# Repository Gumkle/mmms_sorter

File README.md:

### Notes

STM32 Bluepill appears to have bad 3.3V regulator. It is recommended to use external power supply for 3.3V.

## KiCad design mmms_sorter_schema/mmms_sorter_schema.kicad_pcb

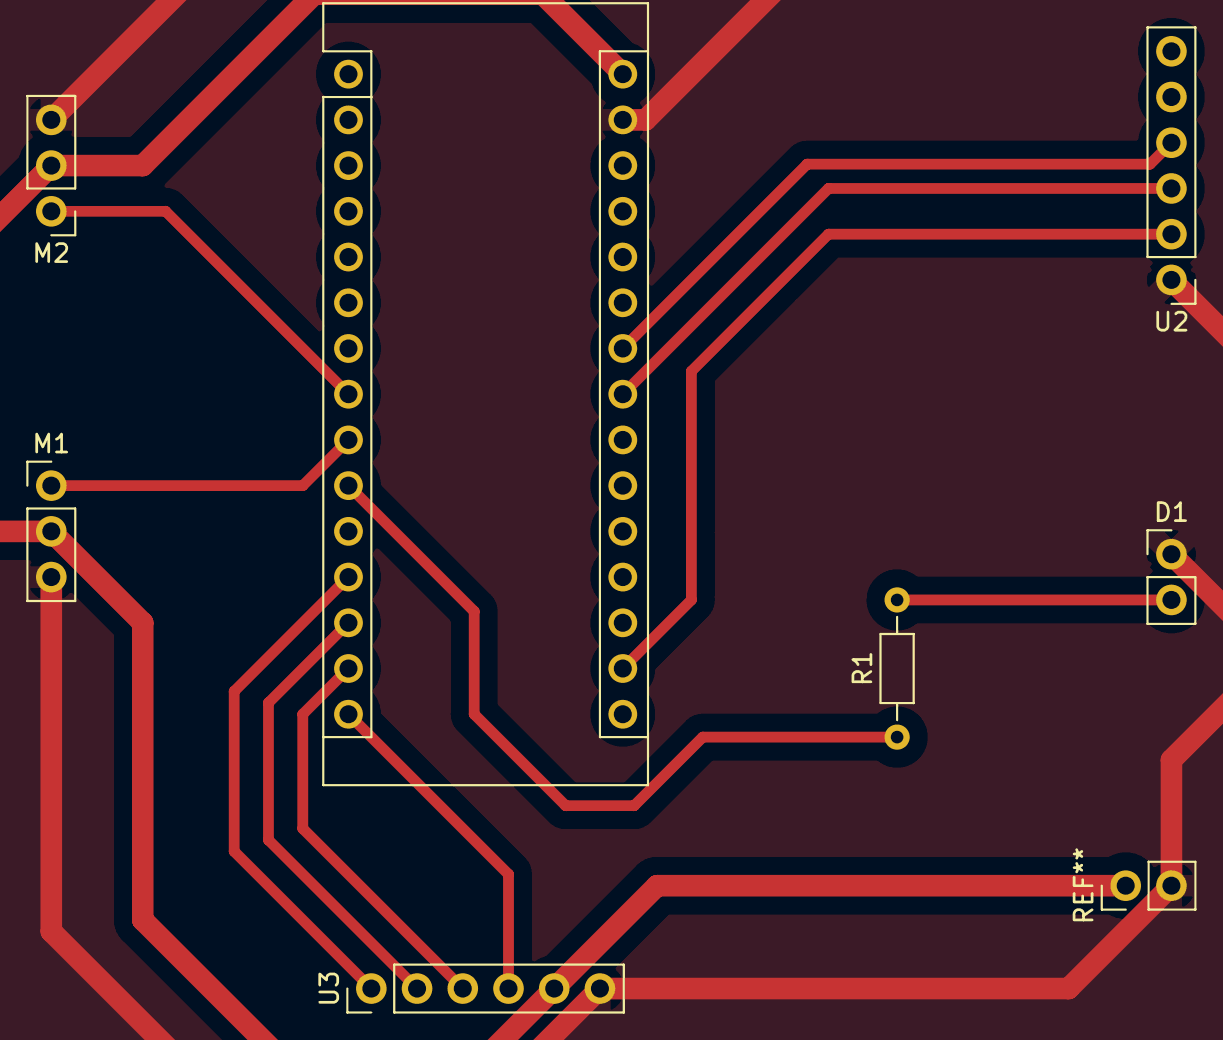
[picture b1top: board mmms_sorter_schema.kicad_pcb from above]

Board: 2 copper layers, 7 parts (0 on the bottom side), 13 nets.

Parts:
A1: Arduino_Nano_v3.x; Arduino_Nano
D1: LED; PinHeader_1x02_P2.54mm_Vertical
M1: Director Servo; PinHeader_1x03_P2.54mm_Vertical
M2: Latch Servo; PinHeader_1x03_P2.54mm_Vertical
R1: 180R; R_Axial_DIN0204_L3.6mm_D1.6mm_P7.62mm_Horizontal
U2: APDS-9960; PinHeader_1x06_P2.54mm_Vertical
U3: ULN2003; PinHeader_1x06_P2.54mm_Vertical

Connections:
+5V: A1.30, M1.2, M2.2, U3.5
GND: A1.29, D1.1, M1.3, M2.3, U2.1, U3.6
unnamed: A1.8, M2.1
unnamed: A1.9, M1.1
unnamed: A1.10, R1.1
unnamed: A1.12, U3.1
unnamed: A1.13, U3.2
unnamed: A1.14, U3.3
unnamed: A1.15, U3.4
unnamed: A1.17, U2.2
unnamed: D1.2, R1.2
SCL: A1.24, U2.4
SDA: A1.23, U2.3

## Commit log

2021-05-03 :sparkles: blank schema, atmega328p program
2021-05-06 Color recognition, electrical schema
2021-05-09 Refine schema and software
2021-06-18 Stm32 program init, error while compiling
2021-06-19 Stm32 fix cmake, input detection
